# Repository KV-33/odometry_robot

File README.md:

# odometry_robot
Робот ориентирующийся по одометрии

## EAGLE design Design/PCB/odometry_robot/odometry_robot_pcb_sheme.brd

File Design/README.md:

# odometry_robot
Раздел для проектирования деталей и компонентов

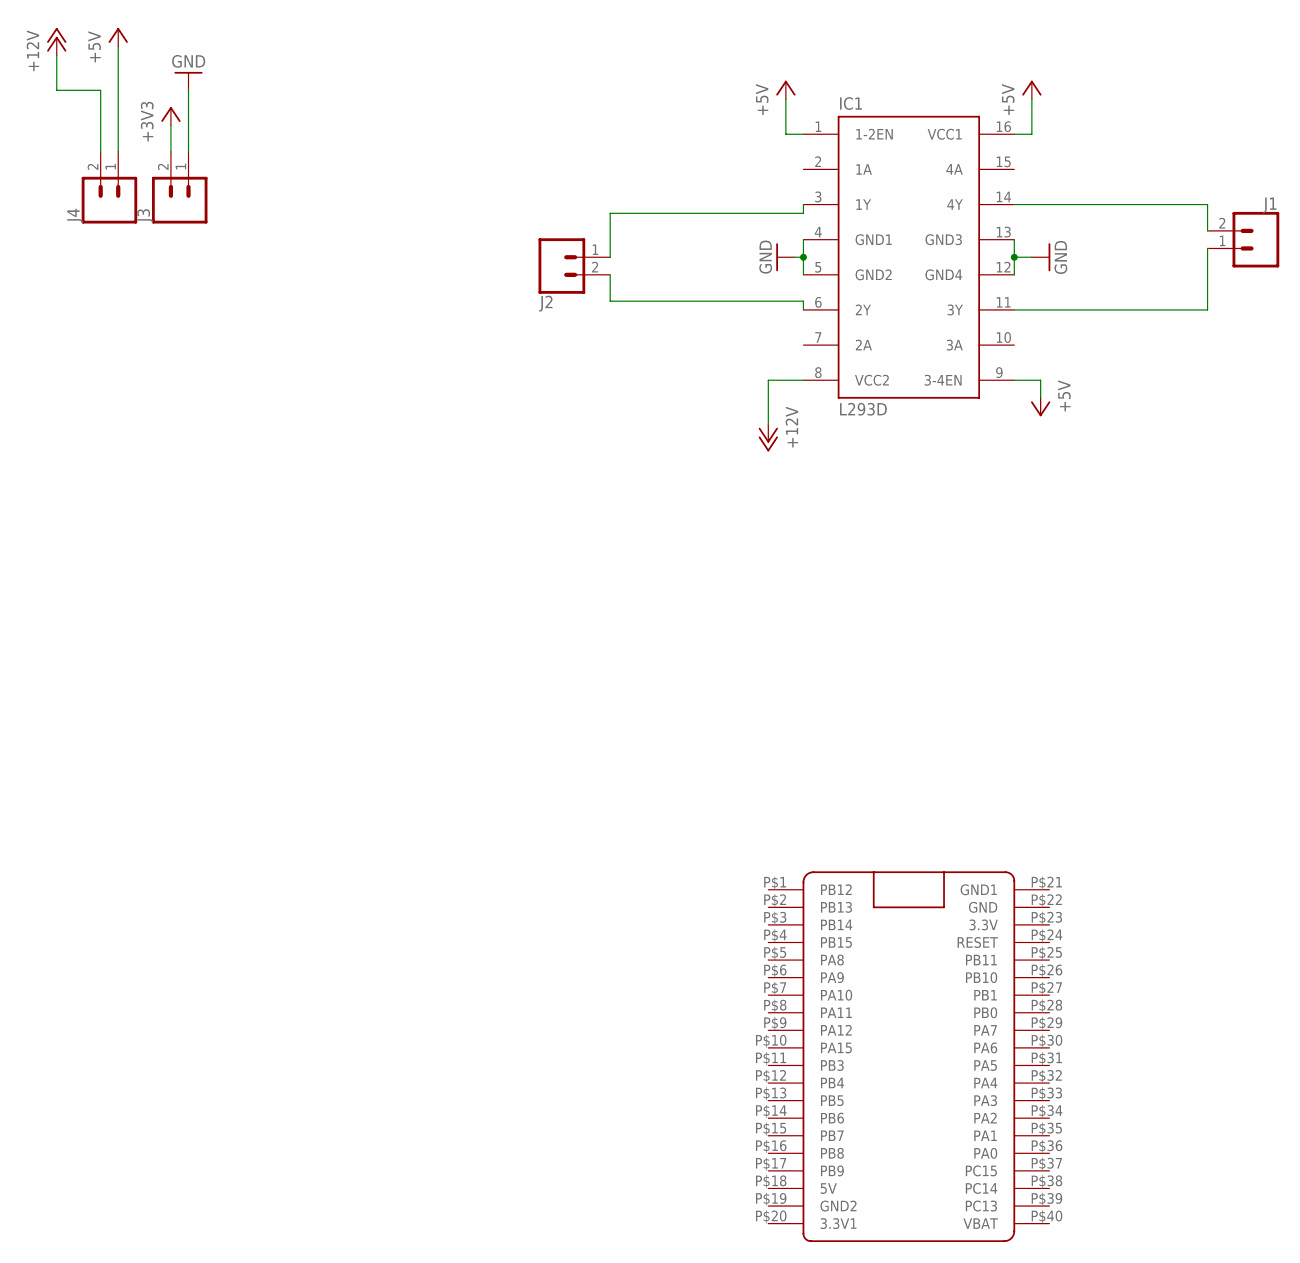
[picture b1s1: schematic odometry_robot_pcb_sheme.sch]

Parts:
IC1: L293D; DIL16
J1, J2, J3, J4: CONN_025MM; SCREWTERMINAL-5MM-2
U$1: BLUE_PILLADVANCED; BLUE_PILL_ADV

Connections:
+3V3: J3.2
+5V: IC1.1 (1-2EN), IC1.9 (3-4EN), IC1.16 (VCC1), J4.1
+12V: IC1.8 (VCC2), J4.2
GND: IC1.4 (GND1), IC1.5 (GND2), IC1.12 (GND4), IC1.13 (GND3), J3.1
GND1: U$1.P$21 (GND1)
unnamed: IC1.3 (1Y), J2.1
unnamed: IC1.6 (2Y), J2.2
unnamed: IC1.14 (4Y), J1.2
unnamed: IC1.11 (3Y), J1.1

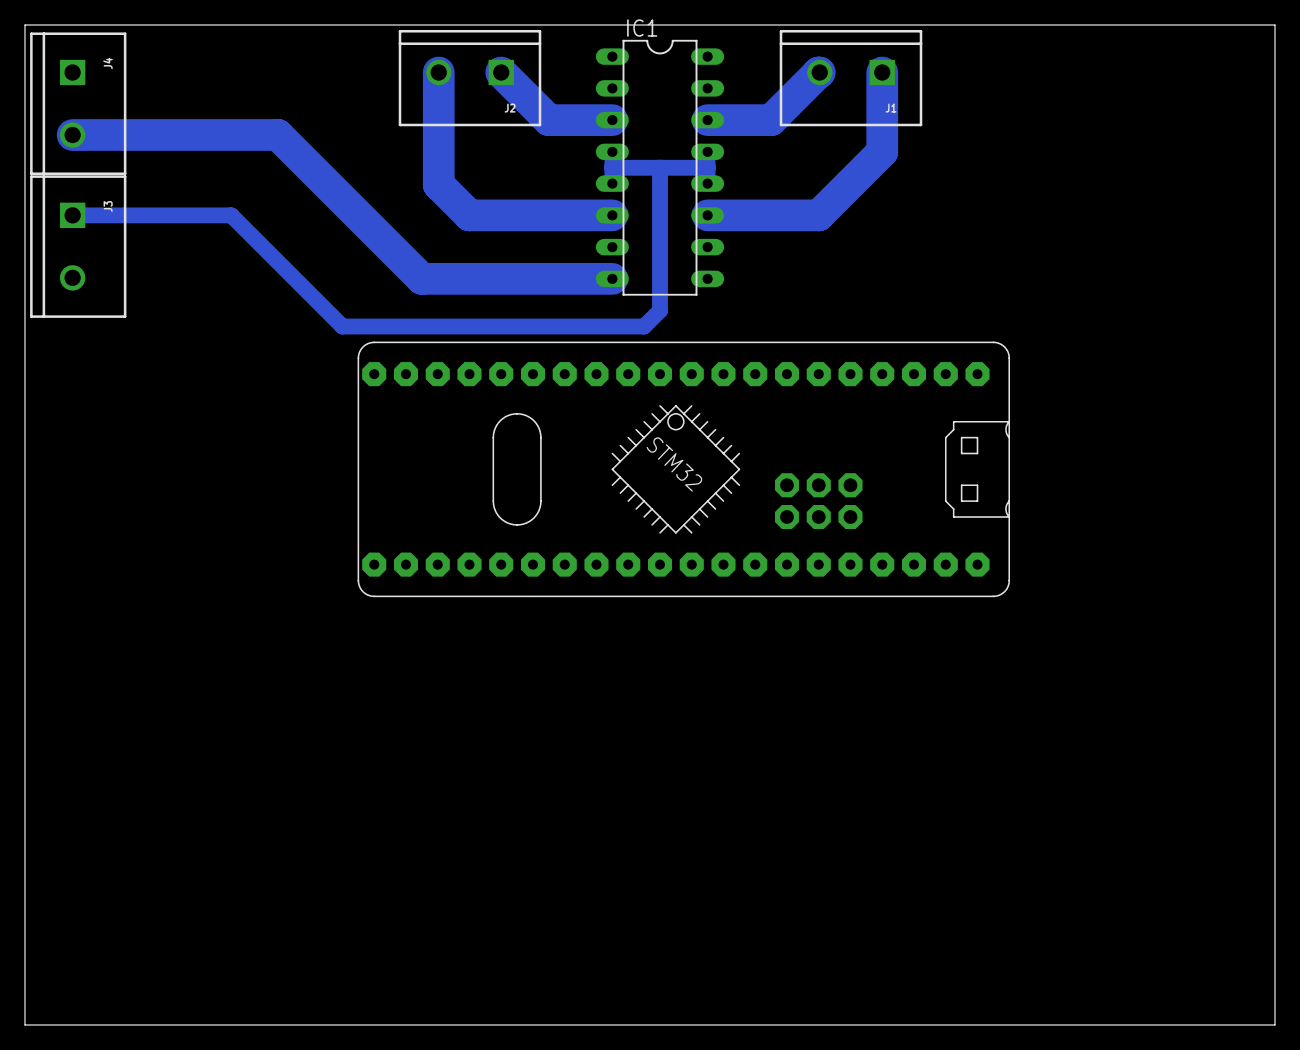
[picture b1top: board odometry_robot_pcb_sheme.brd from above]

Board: 2 copper layers, 100.0 x 80.0 mm, 6 parts (0 on the bottom side), 7 nets.

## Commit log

2020-11-26 add encoder program
2021-02-16 add filesystem
2021-02-16 add shell file directory
2021-02-16 start pcb design
2021-02-17 add workspace

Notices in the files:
parts and their libraries:
SparkFun-Connectors: Licensing: Creative Commons ShareAlike 4.0 International - https://creativecommons.org/licenses/by-sa/4.0
